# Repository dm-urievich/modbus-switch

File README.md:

modbus-swith
============

device for simple control household appliances

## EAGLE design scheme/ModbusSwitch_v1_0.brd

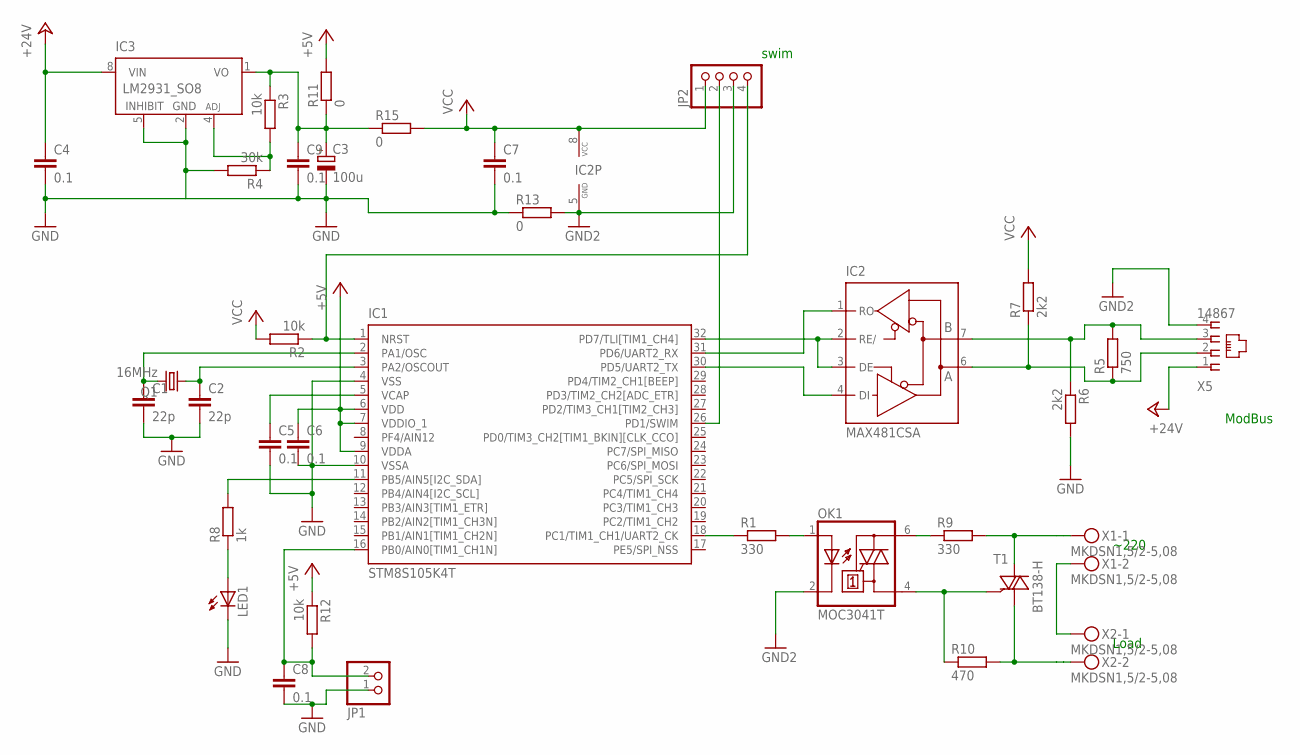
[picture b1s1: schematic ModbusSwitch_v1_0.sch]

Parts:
C1, C2: 22p; C0603
C3: 100u; E2,5-6
C4: 0.1; C1206
C5, C6, C7, C8, C9: 0.1; C0603
IC1: STM8S105K4T; LQFP32-7X7
IC2: MAX481CSA; SO08
IC3: LM2931_SO8; SO-08
JP1: PINHD-1X2/90; 1X02/90
JP2: PINHD-1X4; 1X04
LED1: LED3MM
OK1: MOC3041T; DIL06B
Q1: 16MHz; HC49/S
R1: 330; R0805
R2, R3, R12: 10k; R0603
R4: 30k; R0603
R5: 750; R0603
R6, R7: 2k2; R0603
R8: 1k; R0603
R9: 330; R1206
R10: 470; R1206
R11, R13, R15: 0; R1206
T1: BT138-H; TO220BH
X1, X2: MKDSN1,5/2-5,08
X5: 14867

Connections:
+5V: C6.1, IC1.6 (VDD), IC1.7 (VDDIO_1), IC1.9 (VDDA), R11.2, R12.1
+24V: C4.1, IC3.8 (VIN), X5.1
GND: C1.2, C2.2, C3.-, C4.2, C5.2, C6.2, C7.2, C8.2, C9.2, IC1.4 (VSS), IC1.10 (VSSA), IC3.2 (GND), IC3.5 (INHIBIT), JP1.1, LED1.K (C), R4.2, R6.2, R13.1
GND2: IC2.5 (GND), JP2.3, OK1.2 (C), R13.2, X5.4
GND$1: IC3.3 (GND$1)
GND$2: IC3.6 (GND$2)
GND$3: IC3.7 (GND$3)
unnamed: IC1.32 (PD7/TLI[TIM1_CH4]), IC2.2 (RE/), IC2.3 (DE)
unnamed: IC1.30 (PD5/UART2_TX), IC2.4 (DI)
unnamed: IC1.31 (PD6/UART2_RX), IC2.1 (RO)
unnamed: C5.1, IC1.5 (VCAP)
unnamed: IC1.11 (PB5/AIN5[I2C_SDA]), R8.2
unnamed: LED1.A, R8.1
unnamed: IC1.18 (PC1/TIM1_CH1/UART2_CK), R1.1
unnamed: OK1.1 (A), R1.2
unnamed: OK1.4 (A1), R10.1, T1.G
unnamed: IC1.1 (NRST), JP2.4, R2.1
unnamed: X1.2, X2.1
unnamed: R10.2, T1.T1 (A1), X2.2
unnamed: C3.+, C9.1, IC3.1 (VO), R3.1, R11.1, R15.1
unnamed: C2.1, IC1.3 (PA2/OSCOUT), Q1.1
unnamed: C1.1, IC1.2 (PA1/OSC), Q1.2
unnamed: OK1.6 (A2), R9.1
unnamed: IC2.6 (A), R5.1, R7.1, X5.2
unnamed: R9.2, T1.T2 (A2), X1.1
unnamed: IC3.4 (ADJ), R3.2, R4.1
unnamed: C8.1, IC1.16 (PB0/AIN0[TIM1_CH1N]), JP1.2, R12.2
unnamed: IC1.26 (PD1/SWIM), JP2.2
unnamed: IC2.7 (B), R5.2, R6.1, X5.3
VCC: C7.1, IC2.8 (VCC), JP2.1, R2.2, R7.2, R15.2

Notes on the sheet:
~220
Load
swim
ModBus

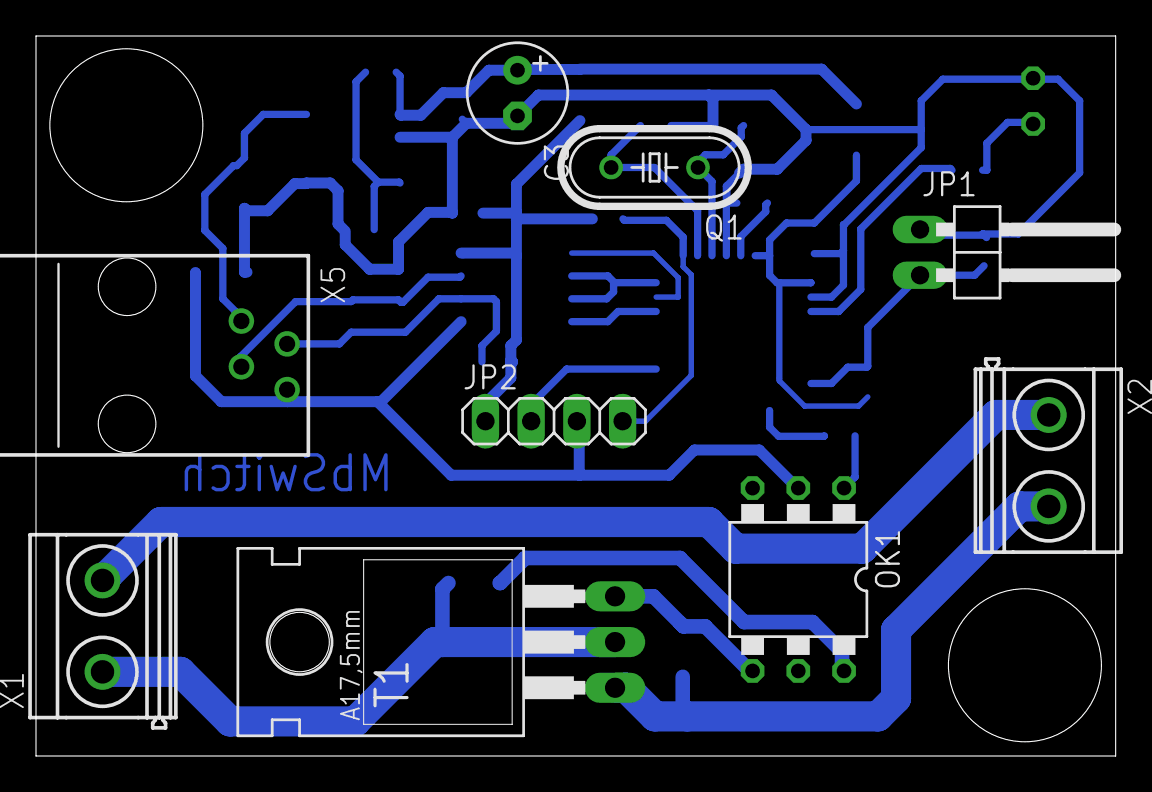
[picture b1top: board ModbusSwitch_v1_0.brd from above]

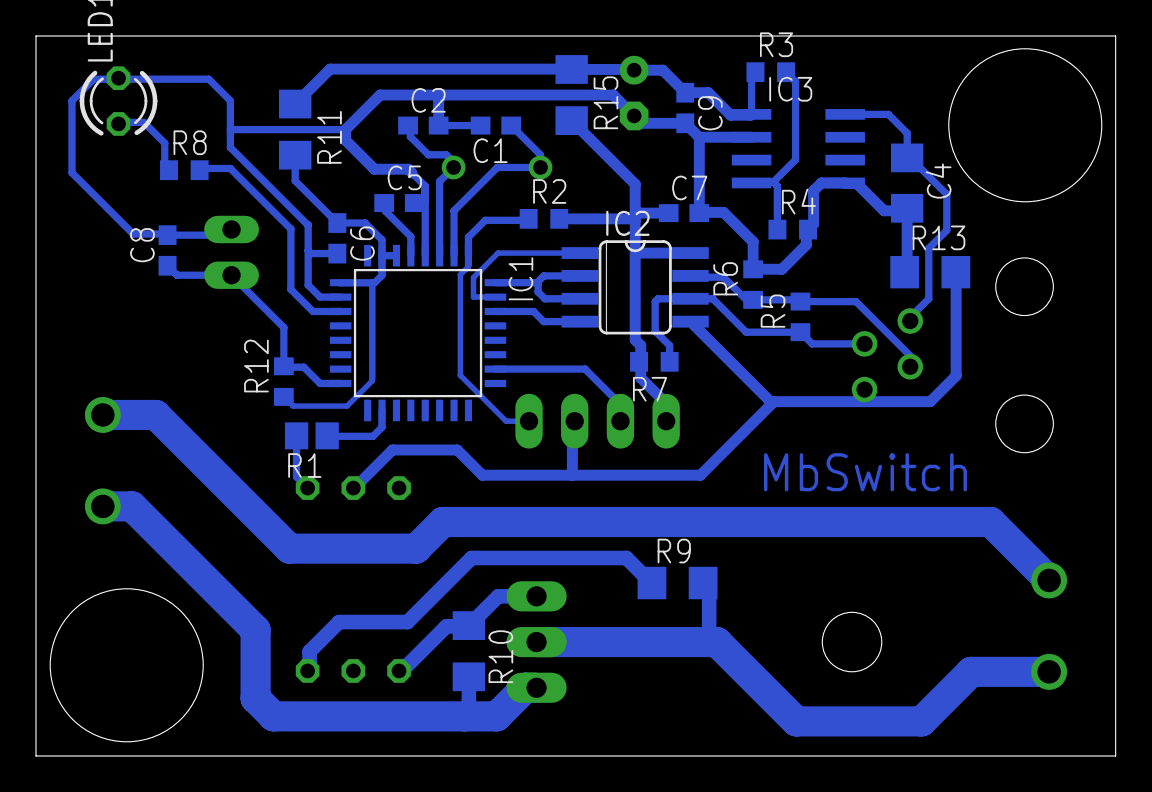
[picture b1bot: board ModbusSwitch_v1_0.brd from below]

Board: 2 copper layers, 60.0 x 40.0 mm, 35 parts (26 on the bottom side), 27 nets.

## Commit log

2014-01-26 add schematic
2014-01-26 add source code, initial version 1.2
2015-05-17 change encoding to UTF-8
2015-05-17 Imported from https://dm-urievich@github.com/dm-urievich/modbus-switch.git
2017-11-29 add schematic in pdf
